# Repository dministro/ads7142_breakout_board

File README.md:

# ADS7142 breakout board (A003.0000017200_DM.ADS7142.BOB)

This is a simple breakout board for
 Texas Instruments ADS7142 (X2QFN) dual-channel, programmable sensor monitor.

[0] - Datasheet: https://www.ti.com/lit/ds/symlink/ads7142.pdf

## Pinout

|#    |Function  |Description   |
|-----|----------|--------------|
|1    |VDDA      |Analog supply input. See AVDD in ref [0]         |
|2    |AIN0      |Channel 0 analog signal input, or positive analog signal input. See AINP/AIN0 in ref [0] |
|3    |AIN1      |Channel 1 analog signal input, or negative analog signal input. See AINM/AIN1 in ref [0] |
|4    |RDY       |See BUSY/RDY in ref [0]                          |
|5    |GND       |Ground for power supply                          |
|6    |GND       |Ground for power supply                          |
|7    |ALERT     |See ALERT in ref [0]                             |
|8    |SDA       |Serial data in/out. See SDA in ref [0]           |
|9    |SCL       |Serial clock. See SCL in ref [0]                 |
|10   |VDD       |Digital I/O supply voltage. See DVDD in ref [0]  |

## Configuration

To select the device address on I2C bus, populate the proper resistor values (R1, R2) as described in the datasheet. See chapter *7.3.6 I2C Address Selector* in [0]

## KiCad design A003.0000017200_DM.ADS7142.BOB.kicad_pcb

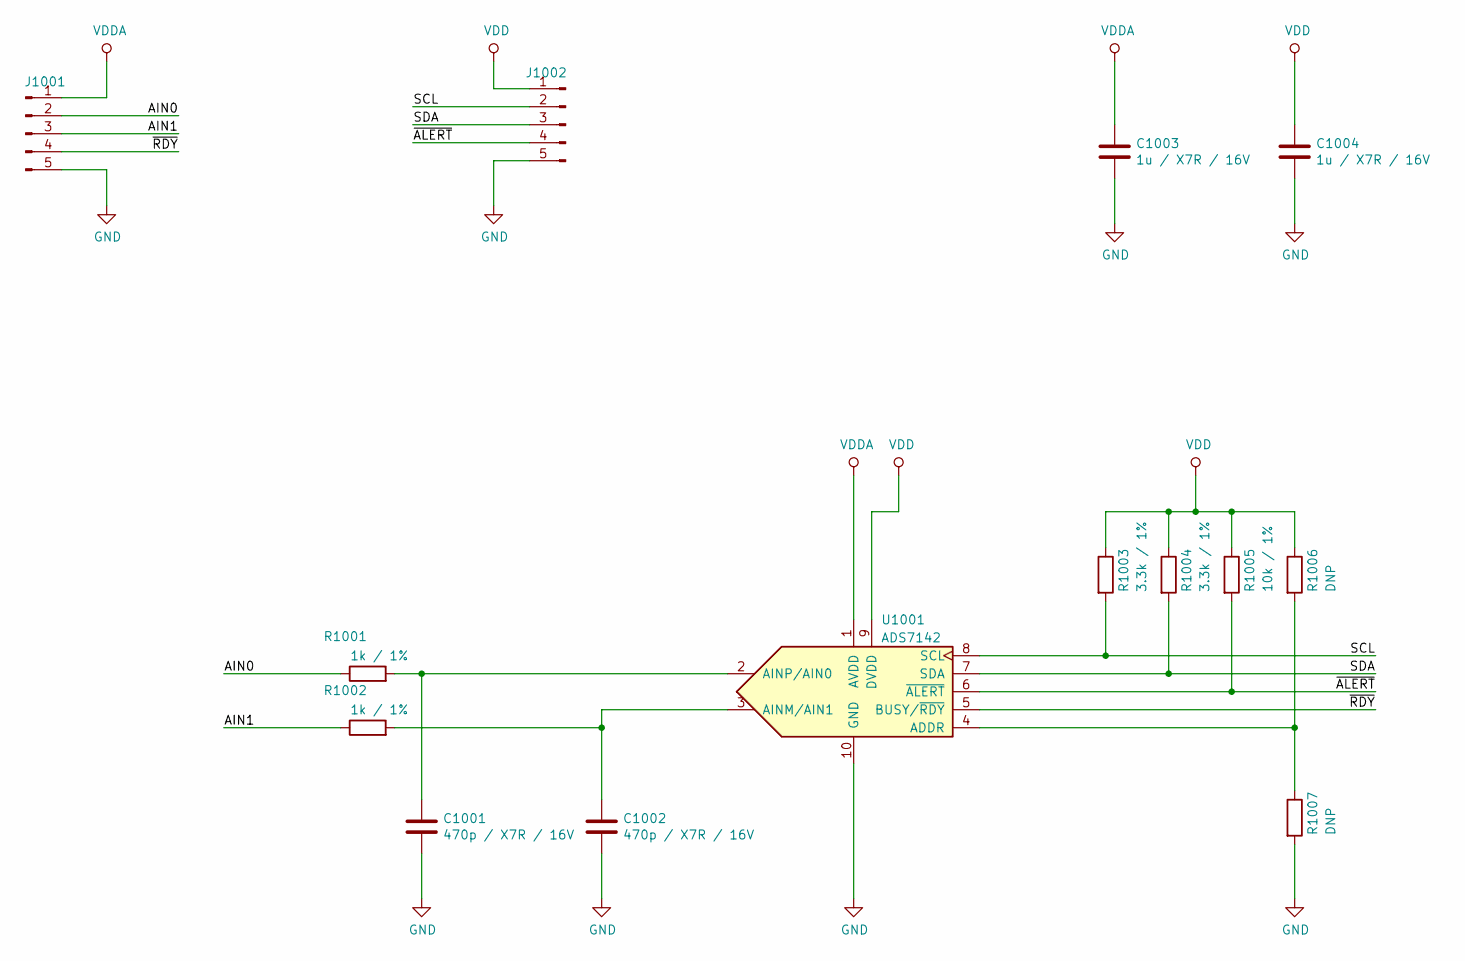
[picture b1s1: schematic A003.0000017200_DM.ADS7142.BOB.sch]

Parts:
C1001, C1002: 470p / X7R / 16V; C_0402; PartNumber C0402C471K4RACTU
C1003, C1004: 1u / X7R / 16V; C_0603; PartNumber C0603C105K4RACTU
J1001, J1002: Conn_01x05_Male; Pin_Header_Straight_1x05_Pitch2.54mm; PartNumber 77311-118-05LF
R1001, R1002: 1k / 1%; R_0402; PartNumber CRCW04021K00FKEDC
R1003, R1004: 3.3k / 1%; R_0603; PartNumber CRCW06033K30FKEAC
R1005: 10k / 1%; R_0603; PartNumber CRCW060310K0FKEAC
R1006, R1007: DNP; R_0603
U1001: ADS7142; Texas_RUG0010A_X2QFN-10_1.5x2mm_Pitch0.5mm; PartNumber ADS7142IRUGT

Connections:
/AIN0: J1001.2, R1001.1
/AIN1: J1001.3, R1002.1
/SCL: J1002.2, R1003.2, U1001.8 (SCL)
/SDA: J1002.3, R1004.2, U1001.7 (SDA)
/~ALERT: J1002.4, R1005.2, U1001.6 (~ALERT)
/~RDY: J1001.4, U1001.5 (BUSY/~RDY)
GND: C1001.2, C1002.2, C1003.2, C1004.2, J1001.5, J1002.5, R1007.2, U1001.10 (GND)
unnamed: C1001.1, R1001.2, U1001.2 (AINP/AIN0)
unnamed: C1002.1, R1002.2, U1001.3 (AINM/AIN1)
unnamed: R1006.2, R1007.1, U1001.4 (ADDR)
VDD: C1004.1, J1002.1, R1003.1, R1004.1, R1005.1, R1006.1, U1001.9 (DVDD)
VDDA: C1003.1, J1001.1, U1001.1 (AVDD)

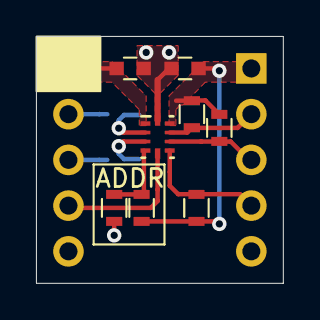
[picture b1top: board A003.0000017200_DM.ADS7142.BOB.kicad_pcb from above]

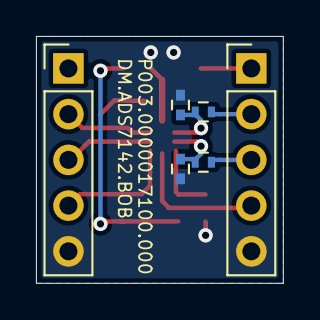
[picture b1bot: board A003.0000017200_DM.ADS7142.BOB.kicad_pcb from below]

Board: 2 copper layers, 13.7 x 13.7 mm, 14 parts (6 on the bottom side), 12 nets.

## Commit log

2021-04-17 added: complete functionality
2021-04-17 added: readme
